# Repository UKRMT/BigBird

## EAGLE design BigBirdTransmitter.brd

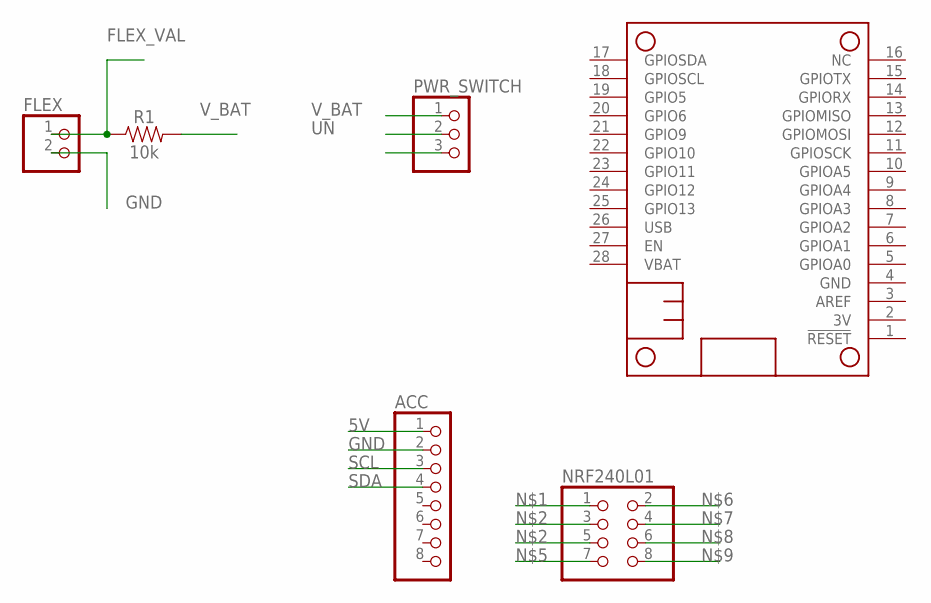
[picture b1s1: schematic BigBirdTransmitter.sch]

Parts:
ACC: PINHD-1X8BIG; 1X08-BIG
FLEX: PINHD-1X2; 1X02
MS1: FEATHERWING
NRF240L01: PINHD-2X4; 2X04
PWR_SWITCH: PINHD-1X3; 1X03
R1: 10k; 0402

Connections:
5V: ACC.1
FLEX_VAL: FLEX.1, R1.1
GND: ACC.2, FLEX.2, MS1.4 (GND)
SCL: ACC.3
SDA: ACC.4
UN: PWR_SWITCH.2
V_BAT: PWR_SWITCH.1, R1.2

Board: 2 copper layers, 6 parts (0 on the bottom side), 3 nets, no tracks yet.

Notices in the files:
parts and their libraries:
SparkFun-Resistors: Licensing: Creative Commons ShareAlike 4.0 International - https://creativecommons.org/licenses/by-sa/4.0
